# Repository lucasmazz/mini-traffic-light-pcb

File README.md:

# Mini Traffic Light PCB

## Introduction

This repository contains the design files for a mini traffic light PCB created using KiCad. The PCB features three vertically arranged LEDs that simulate a standard traffic light. The design also includes the necessary resistors and a connector for easy integration into other projects.

## Schematic Overview

The schematic is designed as follows:

- Each LED (D1, D2, D3) is connected in series with a resistor (R1, R2, R3).
- The anode of each LED is connected to the positive voltage rail through the corresponding resistor.
- The cathode of each LED is connected to the ground.
- The 4-pin connector at the bottom provides external connections, with each pin corresponding to an LED and a common ground.

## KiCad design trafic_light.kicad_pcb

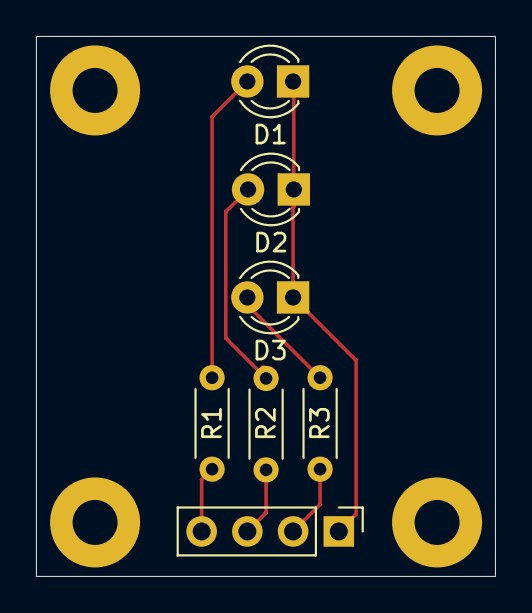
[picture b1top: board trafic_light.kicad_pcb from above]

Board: 2 copper layers, 25.5 x 30.0 mm, 11 parts (0 on the bottom side), 7 nets.

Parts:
D1, D2, D3: LED; LED_D3.0mm
H1, H2, H3, H4: MountingHole; MountingHole_2.5mm_Pad
J1: Conn_01x04; PinHeader_1x04_P2.54mm_Vertical
R1, R2, R3: R; R_Axial_DIN0204_L3.6mm_D1.6mm_P5.08mm_Horizontal

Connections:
unnamed: D3.2 (A), R3.2
unnamed: D1.1 (K), D2.1 (K), D3.1 (K), J1.1
unnamed: D2.2 (A), R2.2
unnamed: D1.2 (A), R1.2
unnamed: J1.2, R3.1
unnamed: J1.3, R2.1
unnamed: J1.4, R1.1

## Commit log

2024-08-13 feat: add mini traffic light PCB design files
2024-08-13 docs: add images to illustrate the mini traffic light PCB design
2024-08-13 docs: update README with project overview
